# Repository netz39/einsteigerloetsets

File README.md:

einsteigerloetsets
==================

Alle Einsteigerlötsets liegen hier

Ghost: www.netz39.de/wiki/projects:2013:einsteigerloetset_gespenst

  * Ghost ist die Version, die für selbst hergestellte PCBs gedacht ist. Achtung beim Ausfrüsen: Der Ausdruck des .svg hat nicht Originalgröße -- muss noch gefixt werden, wahrscheinlich Pixel-Problem.
  * Ghost2 ist keine arbeitsfähige Version (erste Versuche für eine bestellfähige Version)
  * Ghost_USB-B-micro - bestellfähige Version mit Micro-B-USB-Buchse
  * Ghost_USB-C - bestellfähige Version mit USB-Type-C-Buchse

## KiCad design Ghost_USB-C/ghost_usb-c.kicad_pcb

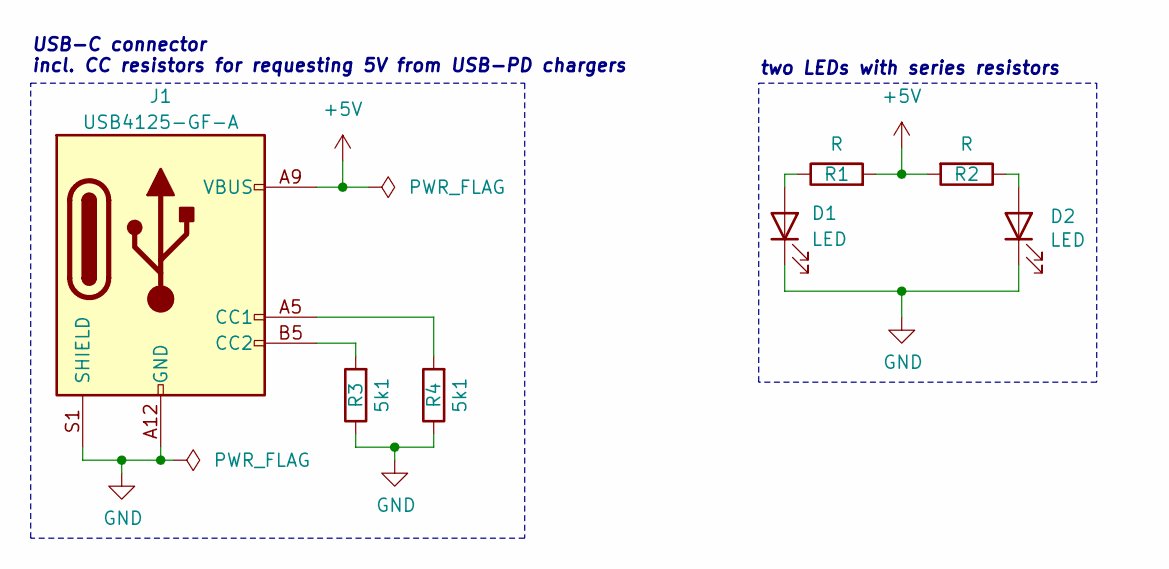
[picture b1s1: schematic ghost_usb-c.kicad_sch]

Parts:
D1, D2: LED; LED_1206_3216Metric_Pad1.42x1.75mm_HandSolder
J1: USB4125-GF-A; USB_C_Receptacle_GCT_USB4125-xx-x_6P_TopMnt_Horizontal
R1, R2: R; R_Axial_DIN0207_L6.3mm_D2.5mm_P10.16mm_Horizontal
R3, R4: 5k1; R_0603_1608Metric_Pad0.98x0.95mm_HandSolder

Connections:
+5V: J1.A9 (VBUS), J1.B9 (VBUS), R1.2, R2.2
GND: D1.1 (K), D2.1 (K), J1.A12 (GND), J1.B12 (GND), J1.S1 (SHIELD), R3.1, R4.1
unnamed: D1.2 (A), R1.1
unnamed: D2.2 (A), R2.1
unnamed: J1.A5 (CC1), R4.2
unnamed: J1.B5 (CC2), R3.2

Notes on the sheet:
USB-C connector incl. CC resistors for requesting 5V from USB-PD chargers
two LEDs with series resistors

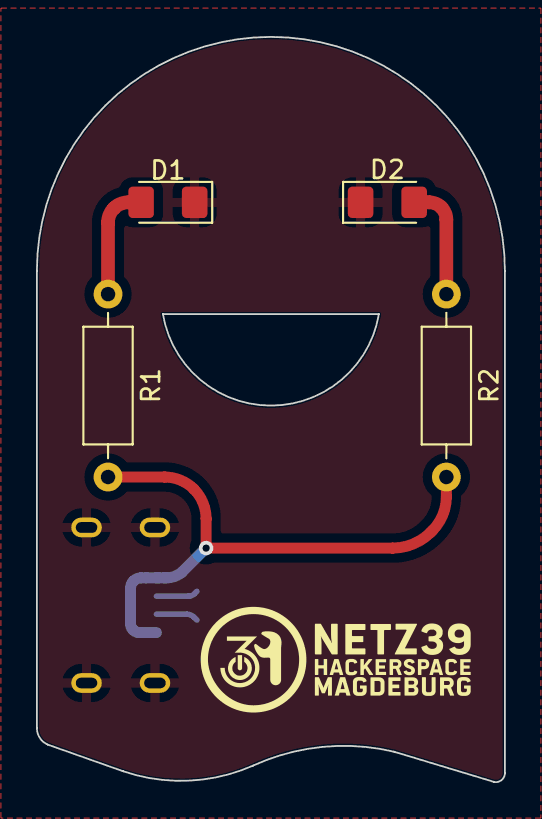
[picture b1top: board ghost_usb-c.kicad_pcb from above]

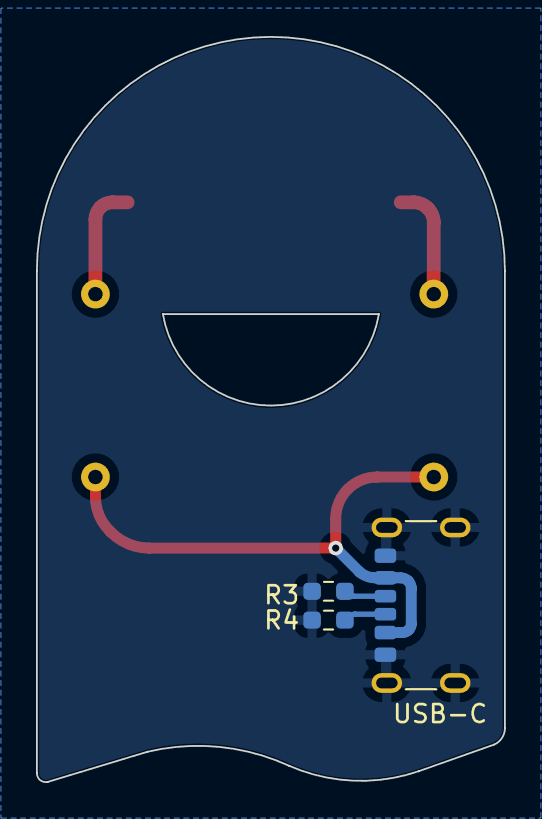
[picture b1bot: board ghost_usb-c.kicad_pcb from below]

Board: 2 copper layers, 26.0 x 41.4 mm, 8 parts (3 on the bottom side), 6 nets.

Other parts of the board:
svg2mod: G***; ghost_silk_n39

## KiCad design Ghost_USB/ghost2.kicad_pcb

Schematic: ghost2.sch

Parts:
D1, D2: LED; LED_PLCC-2
J1: USB_B_Micro; USB_Micro-B_Amphenol_10103594-0001LF_Horizontal
R1, R2: R; R_Axial_DIN0207_L6.3mm_D2.5mm_P10.16mm_Horizontal

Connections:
GND: J1.5 (GND), J1.6 (Shield), R1.1, R2.1
unnamed: D1.2, R1.2
unnamed: D2.2, R2.2
VCC: D1.1, D2.1, J1.1 (VBUS)

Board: 2 copper layers, 6 parts (1 on the bottom side), 4 nets, no tracks yet.

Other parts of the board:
svg2mod: G***; ghost_edge

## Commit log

2013-09-20 Initiale Files:
    Ghost
    1Hz-555-Oszi
2013-09-20 Lötset Ghost: Milling- und Etch-Linien
2013-09-20 * Meta-Infos, Lizenz * Vacuum
2013-09-21 10 Geister auf einer Platine
2013-09-21 Ätzmaske
2013-09-22 Foto der Platine
2013-09-30 Fotos der ersten Charge
2013-12-20 Wiki-Link ins Readme
2013-12-22 Added a louminoused snowman based on the ghost.
2017-07-22 kicad implementierung der geistersets
2019-03-31 first steps for USB-version; import of special kicad-parts, esp. edgecut via svg2mod
2019-04-17 Added crumb peg instructions page
2019-04-28 Footprints angepasst, n39-Logo eingefügt, Fillzone eingefügt
2019-04-29 Umbennenung der Kicad-Dateien in ghost_usb.*; war noch ghost2
2025-02-10 Rename USB-B-micro folder
2025-02-10 Add USB-C variant
